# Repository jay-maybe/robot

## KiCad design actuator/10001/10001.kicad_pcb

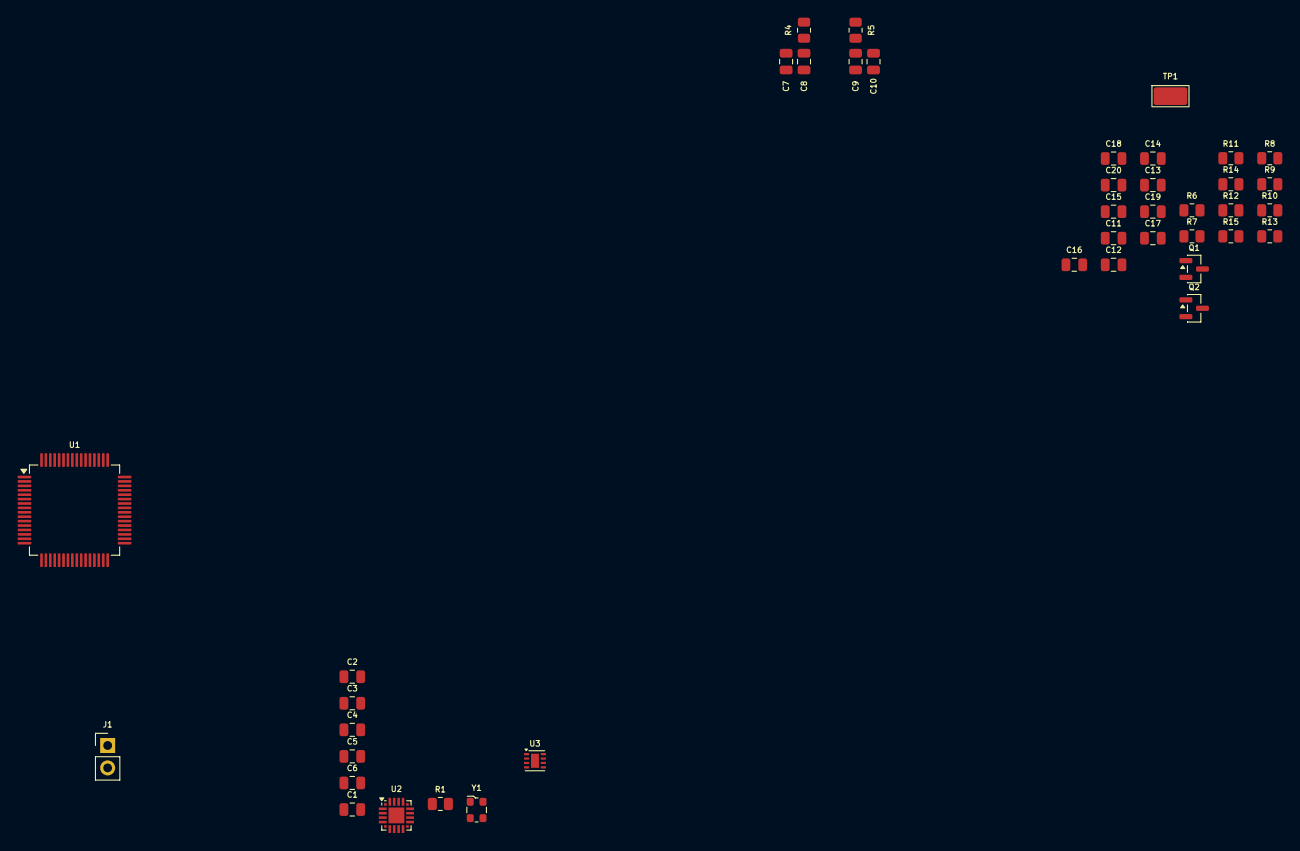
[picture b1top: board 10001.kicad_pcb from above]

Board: 4 copper layers, 41 parts (0 on the bottom side), 18 nets, no tracks yet.

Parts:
C1, C2, C3: 0.1uF; C_0805_2012Metric
C4: 4.7uF; C_0805_2012Metric
C5: 10nF; C_0805_2012Metric
C6: 1uF; C_0805_2012Metric
C7, C8, C9, C10, C11, C12, C13, C14, C15, C16, C17, C18, C19, C20: C; C_0805_2012Metric
J1: Conn_01x02; PinHeader_1x02_P2.54mm_Vertical
Q1, Q2: DMN6140L; SOT-23
R1: 22; R_0805_2012Metric
R4, R5, R6, R7, R8, R11, R12, R13, R14, R15: R; R_0805_2012Metric
R9, R10: 0; R_0805_2012Metric
TP1: 5019; TestPoint_Keystone_5019_Miniature
U1: STM32F030R8Tx; LQFP-64_10x10mm_P0.5mm
U2: CP2102N-Axx-xQFN20; SiliconLabs_QFN-20-1EP_3x3mm_P0.5mm_EP1.8x1.8mm
U3: LDC0851; Texas_DSG0008A_WSON-8-1EP_2x2mm_P0.5mm_EP0.9x1.6mm
Y1: ECS-2520MV-xxx-xx; Oscillator_SMD_ECS_2520MV-xxx-xx-4Pin_2.5x2.0mm

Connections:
+3.3V: C1.1, C2.1, C3.1, C4.1, C5.1, C6.1, U1.1 (VDD), U1.13 (VDDA), U1.32 (VDD), U1.64 (VDD), U3.6 (EN), U3.8 (VDD), Y1.4 (VDD)
+5V: C16.1, C18.1, C20.1, R14.1
/Buck Converter/COMP: C17.1, C19.1
/Buck Converter/FB: C19.2, R13.2, R14.2, R15.1
/Buck Converter/SW: C14.2, Q1.2 (S), Q2.3 (D), R11.1
GND: C1.2, C2.2, C3.2, C4.2, C5.2, C6.2, C7.2, C8.2, C9.2, C10.2, C11.1, C12.1, C13.2, C15.2, C16.2, C18.2, C20.2, R7.2, R8.1, R12.2, R15.2, U1.12 (VSSA), U1.31 (VSS), U1.63 (VSS), U2.3 (GND), U2.12 (GND), U2.21 (GND), U3.7 (GND), U3.9 (GND_EP), Y1.2 (GND)
unnamed: C8.1, R4.2
unnamed: C9.1, R5.2
unnamed: C17.2, R13.1
unnamed: C10.1, Q1.3 (D), R5.1, R6.1
unnamed: Q1.1 (G), R9.2
unnamed: Q2.1 (G), R10.2
unnamed: Q2.2 (S), R12.1
unnamed: R1.2, U1.5 (PF0)
unnamed: C15.1, R11.2
unnamed: R6.2, R7.1
unnamed: R1.1, Y1.3 (OUT)
VBAT: C7.1, R4.1

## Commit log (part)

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2026-06-10 epsode 1
2026-06-19 episode 1 content
